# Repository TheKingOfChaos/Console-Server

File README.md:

# USB Console Server — KiCad 10 project

48 RS-232 console ports on one Raspberry Pi: three identical boards, 16 ports each.
Built from the design record of 2026-10-10. KiCad 10.0.7. **This is Rev B** (git tag `rev-A` is the first board).

| | State |
|---|---|
| Schematic | Complete, 7 sheets (FT4232H cluster reused 4×). ERC: **0 violations** at all severities. |
| Netlist | Checked pin-by-pin against the design intent (`tools/verify_netlist.py`): 255 nets, 0 mismatches. |
| PCB | **150 × 155 mm**, 4 layers, all 361 footprints placed, **fully routed**, ~3330 track segments, ~1170 vias. USB pairs coupled, length-matched and all on F.Cu (below). |
| PCB DRC | **0 errors, 0 unconnected**, 0 schematic-parity issues. Warnings: silkscreen overlaps only. |
| BOM | `bom/usb-console-server_bom.csv`. Every line has an LCSC number. |

## What changed in Rev B

- **Bring up each section on its own.** Every section gets its power through a **3-pin header: 1 = supply, 2 = section, 3 = GND**:

  | Header | Section | Supply |
  |---|---|---|
  | J11 | 5 V buck (input side) | +24V |
  | J12 | 3.3 V buck (input side) | +24V |
  | J13 | USB hub, its EEPROM and crystal (+3V3_HUB) | +3.3V |
  | J14–J17 | FT1–FT4 clusters: FT4232H, EEPROM, both MAX3232E (VCC3) | +3.3V |

  - **Jumper on 1–2** = normal running (7 jumper caps per board, LCSC C100114).
  - **Jumper off**: the section is unpowered. Put an ammeter across 1–2 to read its current, or feed it from a bench supply on 2–3.
  - A jumper put on 2–3 by mistake only grounds the dead section; it cannot short a supply.
  - The Pi needs no header: it is simply not plugged in for early bring-up.
- **Power LEDs** (green, ~1 mA) on +24V, +5V, +3.3V, +3V3_MCU (a labelled column on the left edge), PI_5V and the MCU heartbeat (right of the Pi), the hub (by J13) and each cluster (by its header).
- **Current and voltage sense:** an INA219 behind a shunt on each buck output, 5 mΩ on +5V (U23, I²C 0x40) and 10 mΩ on +3.3V (U24, 0x41). They sit on the MCU's own I²C bus (PA5/PA6, bit-banged, powered from +3V3_MCU), which replaces the old 5 V / 3.3 V ADC dividers. The buck feedback is taken before the shunt.
- **24 V screw terminal J10** (5.08 mm, 2-pin, 18 A) on the left edge, wired to +24V_RAW like the chain connectors: wire up one board, and the chain feeds the rest.
- **MCU UART header J19** (TX PB2 – GND – RX PB3). It shares the SPARE lines of the link, so debug one board at a time.
- **Test points** for each cluster's VCC3 and the INA bus (36 in total).
- **Layout:** the board grew to 150 × 155 mm. The hub moved to the top middle, so the four USB pairs drop straight down to their clusters, all on F.Cu with no vias. Each buck's power stage (inductor, catch diode, output caps, shunt, INA219) is now placed by hand: in Rev A the autoplacer had put the output caps 70 mm from the inductors.

## Sheets

| Sheet | Contents |
|---|---|
| `power` | 24 V terminal J10, input protection (F2 → Q2 → D3 → C46), board-to-board power J3/J4, 5 V and 3.3 V bucks behind bring-up headers J11/J12, shunts + INA219s, rail LEDs, LM317 MCU rail |
| `pi` | 2×20 Pi socket, LM74700 ideal diode + Q1, PI_5V bulk + TVS, HAT ID EEPROM, Pi console SP3232 + J6 |
| `hub` | USB-C, PRTR5V0U2F (inline), USB2514BI in I²C-EEPROM mode, 24 MHz crystal, 24LC02B |
| `ftdi` (×4: FT1–FT4) | FT4232HL, 12 MHz crystal, 93LC46B, two MAX3232E → 4 RS-232 ports |
| `ports` | One HC-RJ45-059D 2×8 block (16 units + shell), shield 0R / 1M / C option |
| `mcu` | ATtiny3216, ID straps, 24 V divider, JP2, INA bus pull-ups, status LED, UPDI, UART header J19, inter-board signal link J8/J9 |

Reference designators the record names are kept: F2, Q1, Q2, R9, R28, R34, R43, D3, D4, C24, C46, C62, C63, C174, X1, JP2, U10–U17.

## Decisions and departures from the record — please review

1. **RJ45 quantity.** LCSC C46261623 is a single 2×8 ganged block with all 16 jacks (~115 mm wide), not a 2-jack block. The BOM has **1 per board**, not 8.
2. **Buck converters** (the record leaves them open). **TPS54560B** (+5V, 5 A) and **TPS54360B** (+3.3V, 3.5 A): both 60 V-rated (above the 42.1 V TVS clamp), with Eco-mode pulse skipping, so they are stable unloaded on boards 2 and 3. Both run at 400 kHz, with EN left open (internal pull-up).
   **Compensation (16.9k / 4.7 nF / 47 pF) is a starting point. Re-derive it in TI WEBENCH** for the chosen L and Cout.
   Inductors are TAI-TECH TMPC1265HP-100MG-D (5 V, Isat 15.5 A; SRP1265A-100M equivalent, same 13.5 × 12.5 mm body) and SRP7028A-100M (3.3 V, Isat 6 A). Output caps are 22 µF/25 V 1206 (a JLCPCB Basic part): 4 on +5V, 3 on +3.3V.
   The LMR33630 was rejected: its 36 V rating is below the clamp.
3. **USB2514B CRFILT/PLLFILT.** The record says 0.01 µF + 0.1 µF. The datasheet asks for ≥1.0 µF low-ESR on each. **Fitted 1 µF + 100 nF. Confirm.**
4. **LM74700 VCAP** goes to ANODE (one of the record's open items; resolved per the datasheet).
5. **Pi mounting: face down on top of the board** (your choice, option B).
   - The Pi sits above our board on four M2.5 × 11 mm standoffs (H5–H8), upside down: its own GPIO header plugs down into J2, a 2×20 socket on our top side.
   - It is turned 90° so the USB/Ethernet block hangs past our top edge. The side edges stay free for the chain, so the Pi board can sit anywhere in it.
   - The Pi's underside faces up, so the **microSD card is reachable without unbolting anything**. It sits at the end toward the FTDI clusters.
   - The builder checks that J2 pad *n* sits under Pi GPIO pin *n* (the face-down Pi is a mirror image of its own top view).
   - The Pi's components face down into the 11 mm gap. **Only parts ≤ 3 mm tall sit under it**, and the builder checks this. The Pi 4 PoE-header spot (approximate, on User.Drawings) is kept clear.
   - The Pi outline and jack block are drawn on User.Drawings and F.Fab.
   - The cabinet needs ~23 mm of clearance beyond board 1's top edge for the jacks and cables.
6. **Board-to-board connectors.** With KiCad's stock right-angle header (J3/J8, right edge) and socket (J4/J9, left edge), pin *n* lands at the same height on both footprints. So the numbering runs the same direction, unlike the record's note, which describes its own footprints. The builder asserts this.
7. **RJ45 port mapping.** Column *j* (0–7, left to right) is P(2j+1) = pads 24j+1..8 and P(2j+2) = pads 24j+9..16. Pads 1/16 sit at the same end, matching the record. **Which physical jack (upper or lower) carries pads 1–8 is not in the vendor data.** The 3–6 loopback at bring-up settles it.
8. **Added parts** the record didn't specify:
   - RESET_REQ: 100k pull-down, for a defined level on boards without a Pi.
   - HAT EEPROM: ID_SD/ID_SC 3.9k pull-ups, plus a WP pull-up and write-enable jumper.
   - VBUS_DET: 47k/100k divider.
   - USB shield: 1M ‖ 4.7 nF to GND.
   - Hub RESET_N: 10k pull-up and 100 nF.
   - Hub LOCAL_PWR: 10k pull-up.
9. **Net classes:**
   - `USB_90R` (0.16 mm width / 0.15 mm gap) assumes JLCPCB's JLC04161H-3313 stackup. Confirm it in their impedance calculator.
   - `HV_24V`: 0.8 mm width, 0.3 mm clearance.
   - `Power`: 0.6 mm width.
10. **USB port swap (PRTSP) — must be set in the hub EEPROM.** On the hub and on the FT4232Hs, D− sits above D+ on the faces that point at each other, so a coupled pair would have to cross over. Instead, D+/D− are swapped at the hub's downstream pins in the schematic (pin 1 = D+ of port 1, pin 2 = D−, and so on for pins 1–4 and 6–9).
    - The USB2514B undoes the swap internally when **PRTSP (register 0xFA) = 0x1E** (ports 1–4) in the 24LC02B image.
    - **Without it, none of the FT4232Hs will enumerate.**
    - The upstream port is not swapped (bit 0 stays 0).

## Board layout

150 × 155 mm: the 115 mm RJ45 block along the bottom, a slotted M3 chassis hole in each corner.

- **Bottom edge.** The RJ45 block, front flush with the edge. Silkscreen `P02 / P01`, etc. above each column.
- **Middle band.** FT1–FT4 clusters, each over its own two jack columns (FT1 at the P01 end): MAX3232E row next to the jacks, then the FT4232H with its crystal and decoupling, then the EEPROM. Above each cluster: its bring-up header (`FT1 3V3` ...) and power LED.
- **Edge strips beside the clusters.** Board-to-board connectors: J8 (link) and J3 (24 V) headers on the right, J9/J4 sockets on the left, same heights. J10, the 24 V screw terminal, sits above J9 with its wire openings at the left edge.
- **Top left: power.** J11/J12 bring-up headers and the rail LEDs on the left edge; the 5 V buck (U8, L1, D1, output caps, shunt R10, INA219 U23) and below it the 3.3 V buck (U9, L2, D2, caps, R11, U24); the 24 V protection (F2, Q2, C46) next to the terminal.
- **Top middle: USB.** USB-C J1 on the top edge near the Pi's USB-A ports, the PRTR5V0U2F, the hub U5 with its crystal and EEPROM, J13 (hub bring-up header). A clear corridor below the hub carries the four USB pairs to the clusters.
- **Top right.** The Raspberry Pi, face down above the board (X 84–140, Y 0–65), with its jacks over the top edge; J2 runs down its right side. Under the Pi: the MCU, Pi console transceiver, HAT EEPROM, ideal diode and LM317 (all low parts). In the 10 mm strip right of it: UPDI J7, Pi console J6, MCU UART J19, the PI_5V electrolytics and the MCU / PI5V LEDs.

## Test points

36 bare pads (no BOM cost), all reachable with the Pi fitted. The board builder keeps them out from under the Pi.

| Where | Test points |
|---|---|
| Rails | +24V_RAW, +24V, +5V, +3.3V, +3V3_MCU, PI_5V, PI3.3, and per cluster its VCC3 and 1.8 V VCORE (×4) |
| Ground | by the bucks, by the USB-C input, beside the jacks (scope ground), and one per cluster |
| Buses | PI_SDA / PI_SCL, HUB_SDA / HUB_SCL, INA_SDA / INA_SCL |
| Control | HUB_MR_N, FTDI_RST_N, RESET_REQ, ALERT, VBUS_UP, MCU spare PA7 |
| Pi console | PITXD / PIRXD (TTL side; the RS-232 side is on J6) |

## Stackup and routing

**Stackup** (JLCPCB 4-layer):
- F.Cu: signals, plus ground pour.
- In1.Cu: solid ground plane.
- In2.Cu: signals, plus a +3.3V pour and a +5V band.
- B.Cu: signals, plus ground pour.

**Rules:** JLCPCB standard 4-layer: 0.127 mm track and space, 0.5/0.25 mm signal vias.

**Routing pipeline:** `tools/route.py`, then `tools/close_gaps.py`.

1. **Pre-routing** (locked):
   - every FT4232H ground pin gets an inward stub and a via to the ground plane;
   - the four hub→FT4232H USB pairs are routed first as coupled pairs (`tools/diffpair.py`, 0.16 mm / 0.15 mm gap), see "USB pairs" below.

   This stops anything else boxing those 0.5 mm-pitch pins in.
2. **Freerouting 2.4** routes everything else, with these net-class widths:

   | Net class | Width | Nets |
   |---|---|---|
   | USB_90R | 0.16 mm | USB pairs |
   | Power | 0.3 mm | power nets |
   | HV_24V | 0.5 mm | 24 V |
   | Chain24V | 1.0 mm | the 24 V pass-through between J3 and J4 |
   | HighCurrent | 0.6 mm | 5 V path and switch nodes |

3. **Power copper** carries the real current; the traces only guarantee connectivity:
   - pours on both buck switch nodes, both buck inputs, both buck outputs (up to the shunts) and the ideal-diode input;
   - a 7 mm-wide +5V band on In2 from the 5 V shunt to the Pi, stitched with vias at both ends;
   - an In2 pour per switched section (+3V3_HUB, each cluster's VCC3) over that section.
4. **Ground stitching:** a 4 mm via grid across the board, and a via grid under each FT4232H and the hub.
5. **Cleanup** (`close_gaps.py`), driven by KiCad's own DRC report:
   - joins the autorouter's near misses;
   - gives stranded ground or +3.3V pads a via to their plane or pour;
   - maze-routes anything still open, ripping up the nets that wall it in if needed;
   - removes any via that violates clearance.

**USB pairs (hub → FT4232H), routed as coupled pairs, all on F.Cu over the In1 ground plane, no vias:**

| Port | D+ | D− | Skew |
|---|---|---|---|
| 1 | 97.4 mm | 96.2 mm | 1.1 mm |
| 2 | 82.4 mm | 81.2 mm | 1.1 mm |
| 3 | 83.2 mm | 82.1 mm | 1.1 mm |
| 4 | 89.4 mm | 87.5 mm | 1.9 mm |
| upstream (USB-C → hub) | 17.1 mm | 18.0 mm | 0.9 mm |

- 1–2 mm of skew is ≈ 7–13 ps; USB 2.0 high speed tolerates far more, so no tuning meanders were added.
- The pair router keeps the pairs clear of the bucks' whole power stage and never routes under an IC body.
- This depends on the **PRTSP = 0x1E** hub setting (decision 10).
- Hand fixes after the generated routing (so `build_all.sh` alone does not reproduce this board exactly): FT1's VPHY escapes through a 0.45 mm via at pin 4 (its VCORE B.Cu track was moved 0.55 mm to make room), TP12 moved 0.6 mm, one GND stitching via in an isolated F.Cu pour island.

**Review before ordering:**
- **USB pair impedance:** 0.16 mm / 0.15 mm gap is ≈ 90 Ω differential on JLC04161H-3313 (F.Cu over In1). Confirm it in JLCPCB's impedance calculator.
- **Buck loops:** the power stages are now placed by hand, but still check each input-cap / switch / diode loop against the TPS54x60 layout guide.
- **INA219 shunt routing:** IN+/IN- are routed from the shunt pads by the autorouter; check they are Kelvin connections (from the shunt pads themselves, not from the pour).
- **Autorouted traces:** the routing is generated, so expect some odd detours. Re-run DRC after any hand edit.

## 3D model

- `3d/usb-console-server.step`: the whole board with every part (16 MB), for enclosure design in any CAD tool. `3d/preview.png` is a quick render.
- Rebuild it in KiCad (File > Export > STEP) or with `kicad-cli pcb export step --subst-models usb-console-server.kicad_pcb`; KiCad's standard 3D library must be installed.
- Models that are not in KiCad's library are in `lib/console_server.3dshapes`:
  - **J5, the 16-port RJ45 block, is a simplified envelope** (`tools/rj45_model.py`): no vendor model or drawing exists. The 115 × 28.2 mm outline and port positions match the footprint, but the **25.4 mm height is assumed** (typical for stacked 2×N RJ45). Measure a real part before finalising an enclosure.
  - L2 (SRP7028A) and J1 (HRO TYPE-C-31-M-12 USB-C) use the EasyEDA models for their LCSC parts.
  - `tools/fix_3d_models.py` points L2, J1, U8 and U9 at these files (KiCad 10 renamed or lacks the stock ones).
- The Raspberry Pi is not in the model. It sits face-down on J2.

## Ordering from JLCPCB

`python3 tools/jlc_export.py` writes `jlcpcb/`:

| File | Upload as |
|---|---|
| `usb-console-server_gerbers.zip` | the PCB: 4 layers, 150 × 155 mm, 1.6 mm, impedance control with stackup **JLC04161H-3313** |
| `usb-console-server_bom_jlc.csv` | assembly BOM: 65 lines, every one with an LCSC number (SMD only) |
| `usb-console-server_cpl_jlc.csv` | pick-and-place: 293 parts, all on the top side |
| `usb-console-server_hand_solder.csv` | not uploaded: the through-hole connectors you solder yourself, with LCSC numbers to buy them |
| `usb-console-server_lcsc_order_3boards.csv` | LCSC BOM Tool upload: **every** part for a full set of 3 boards (to build them all yourself) |
| `usb-console-server_lcsc_order_3boards_through_hole_only.csv` | LCSC BOM Tool upload: only the hand-soldered connectors and jumper caps, when JLCPCB assembles the SMD parts |
| `..._5boards.csv`, `..._5boards_through_hole_only.csv` | the same for 5 boards |

- Other board counts: `python3 tools/lcsc_order.py <boards>`. LCSC rounds each line up to its minimum order quantity.
- **Not assembled by JLC:** test points, mounting holes and DNP parts, and every through-hole part (J2 Pi socket, J3/J4 power chain, J5 RJ45 block, J8/J9 link, J6/J7/J19 debug headers, J10 terminal, J11–J17 bring-up headers) plus the 7 jumper caps. These are soldered by hand; see `usb-console-server_hand_solder.csv`.
- **Check every part's rotation in JLC's placement preview.** KiCad and JLC disagree on the zero orientation of some packages (often SOT-223, SOT-23-6, SOIC, the LQFP/QFN ICs, diodes, electrolytics, crystals). Fix any that look wrong in their editor before paying.
- Stock and "extended part" fees change daily; JLC flags missing parts when you upload the BOM.

## Regenerating

Everything is generated from `tools/design.py` (schematic) and `tools/build_pcb.py` (board), which need KiCad 10 with its Python module. `tools/build_all.sh` rebuilds and re-verifies the whole project.

**Rebuilding overwrites the board placement.** Once you start editing the PCB by hand, treat the KiCad files as the source and stop regenerating.

## Bring-up checklist

Start with **every bring-up jumper off** (J11–J17) and no Pi.

1. **24 V input.** 24 V on J10 with a current-limited supply: the 24V and MCU LEDs light, nothing else. Then reverse polarity: nothing downstream may see voltage.
2. **MCU alone** (it runs from its own LM317): UPDI on J7, heartbeat LED, ID straps read with a meter, J19 UART.
3. **5 V buck:** jumper J11. 5V LED on, 5.09 V at TP +5V, stable with no load (it is unloaded on boards 2 and 3 for life). INA219 U23 at 0x40 on the MCU's INA bus.
4. **3.3 V buck:** jumper J12. 3V3 LED on, 3.33 V, INA219 U24 at 0x41.
5. **Hub:** jumper J13 (meter across 1–2 first: expect ~50–100 mA). Program the hub EEPROM (**including PRTSP = 0x1E**), then `lsusb` from a PC shows the hub.
6. **One cluster at a time:** jumper J14 (FT1), check its current on 1–2 (~70–150 mA), `lsusb` shows the FT4232H, program its EEPROM serial (`HUB<b>-P<n>`), then J15–J17.
7. **Pi:** fit it on one board, PI5V LED, `i2cdetect -y 1` shows 0x30.
8. **Loopback** (pin 3 ↔ pin 6) on every port, including one upper and one lower jack early.
9. udev rules.
10. Chain boards 2 and 3.

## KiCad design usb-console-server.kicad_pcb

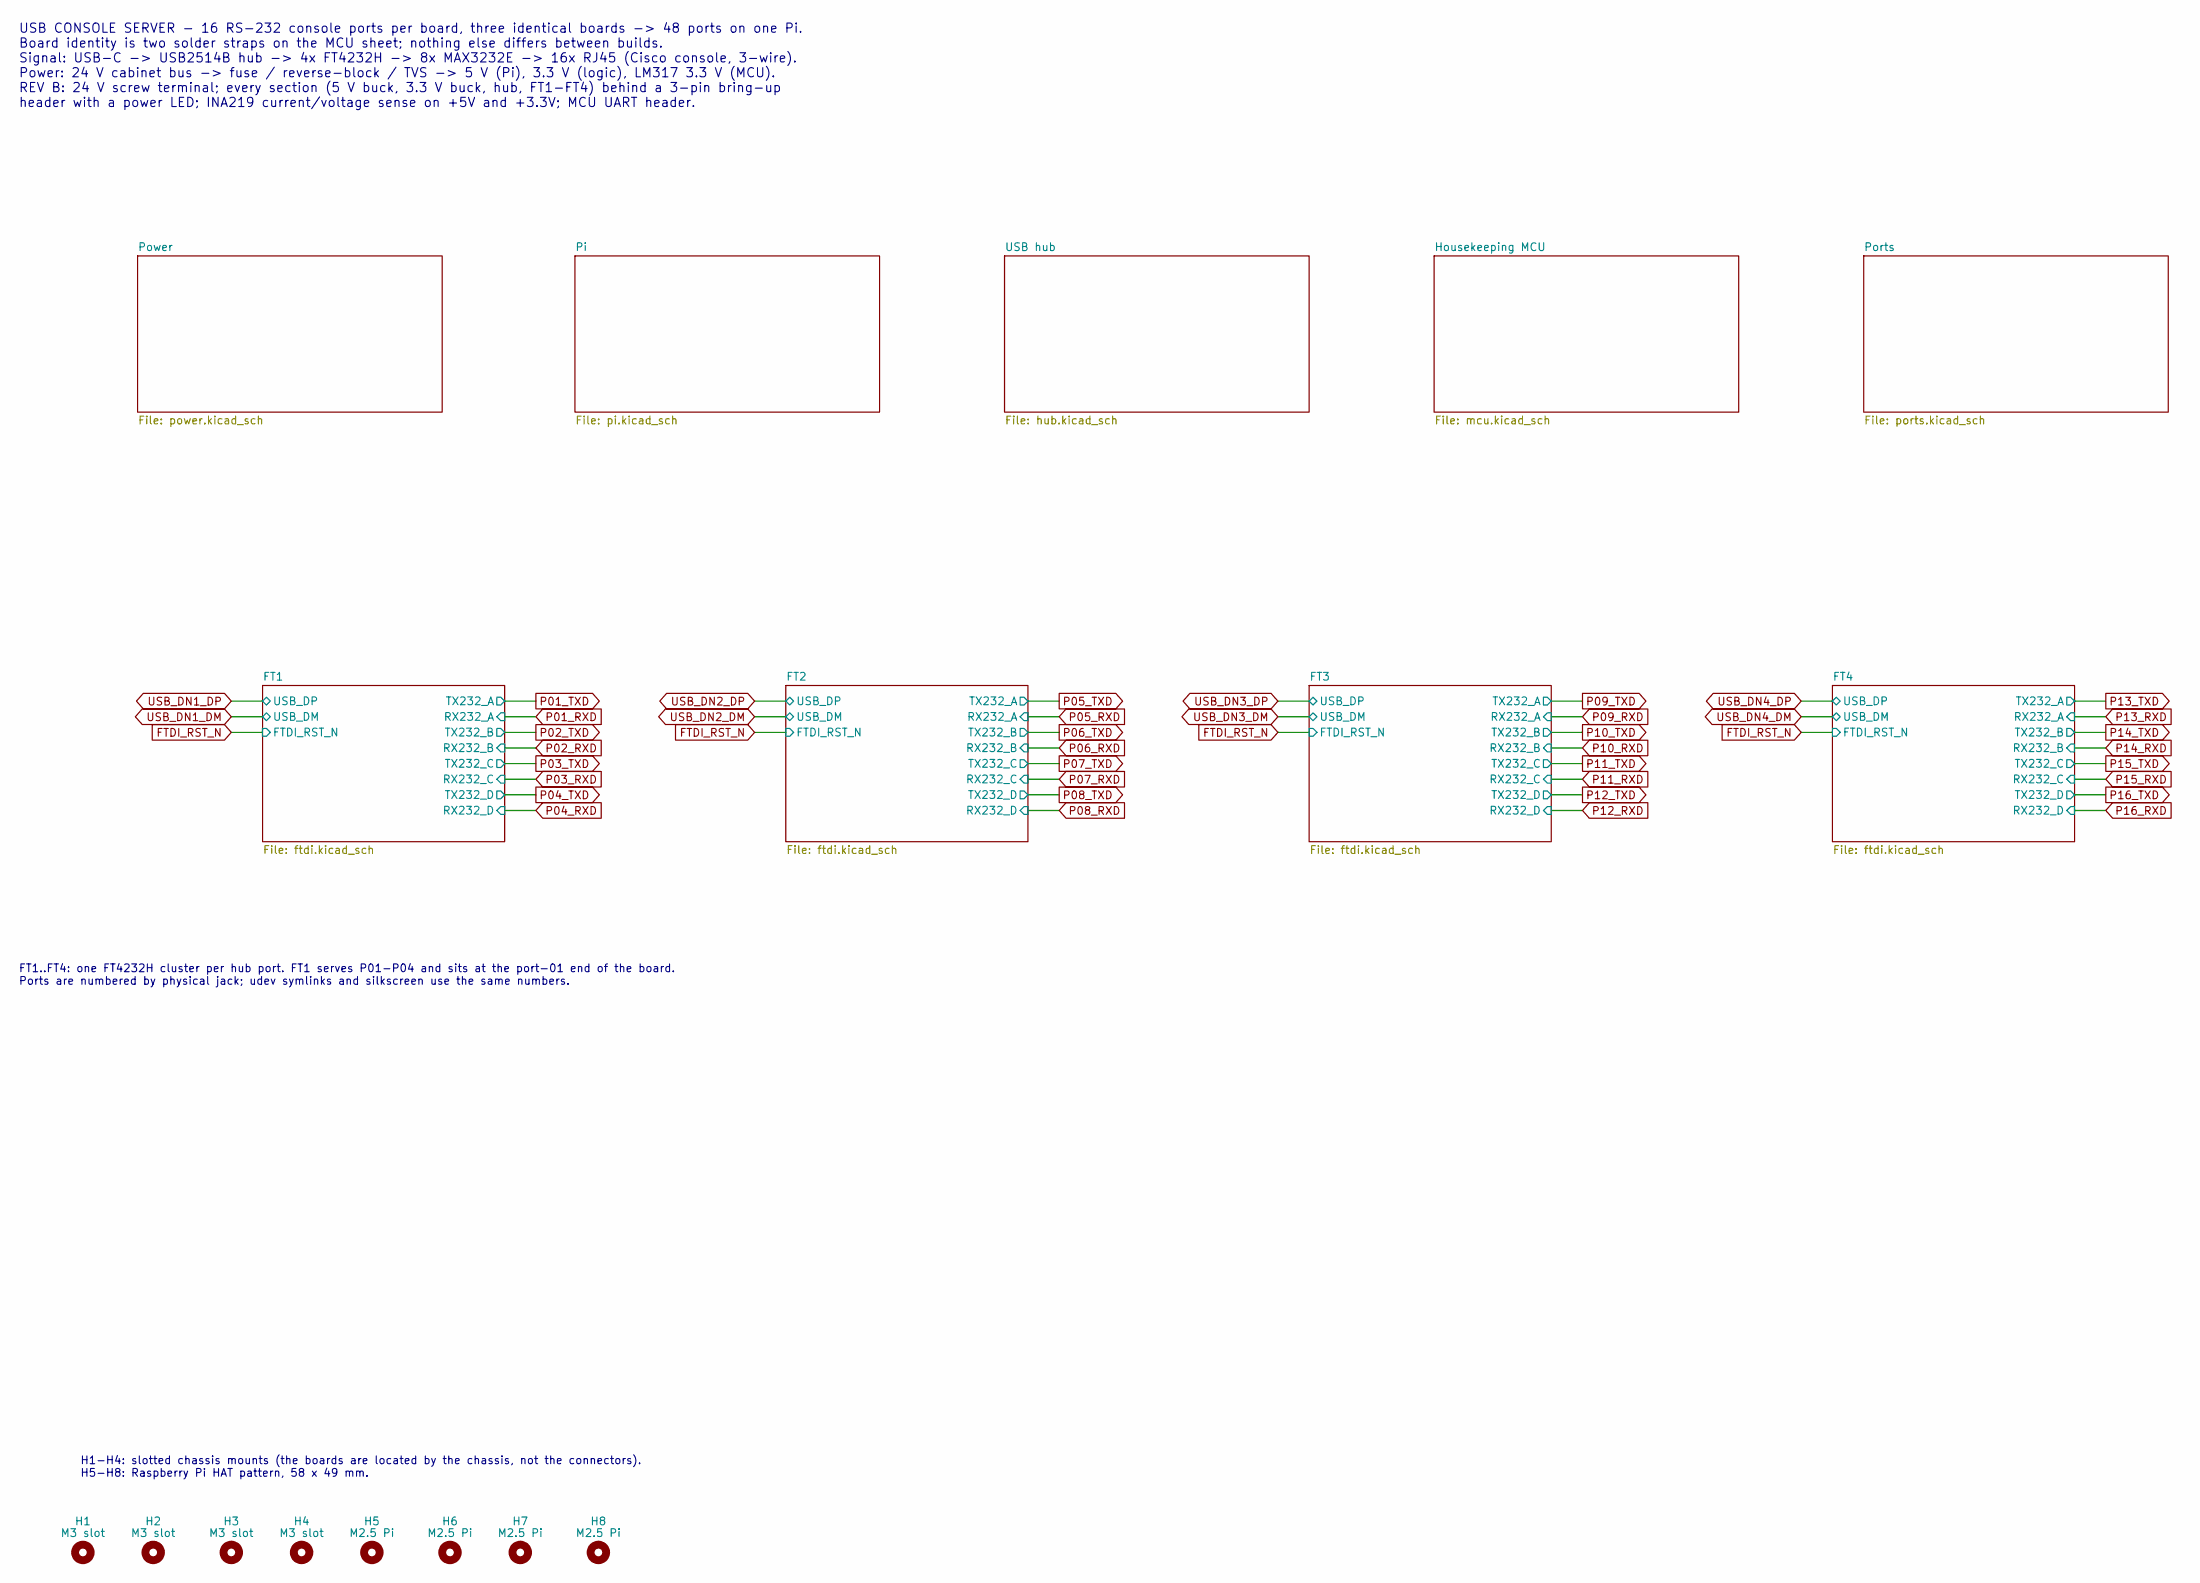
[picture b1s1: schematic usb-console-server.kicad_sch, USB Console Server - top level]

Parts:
H1, H2, H3, H4: M3 slot; MountingSlot_3.2x6mm
H5, H6, H7, H8: M2.5 Pi; MountingHole_2.7mm_M2.5

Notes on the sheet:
USB CONSOLE SERVER - 16 RS-232 console ports per board, three identical boards -> 48 ports on one Pi. Board identity is two solder straps on the MCU sheet; nothing else differs between builds. Signal: USB-C -> USB2514B hub -> 4x FT4232H -> 8x MAX3232E -> 16x RJ45 (Cisco console, 3-wire). Power: 24 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
FT1..FT4: one FT4232H cluster per hub port. FT1 serves P01-P04 and sits at the port-01 end of the board. Ports are numbered by physical jack; udev symlinks and silkscreen use the same numbers.
H1-H4: slotted chassis mounts (the boards are located by the chassis, not the connectors). H5-H8: Raspberry Pi HAT pattern, 58 x 49 mm.

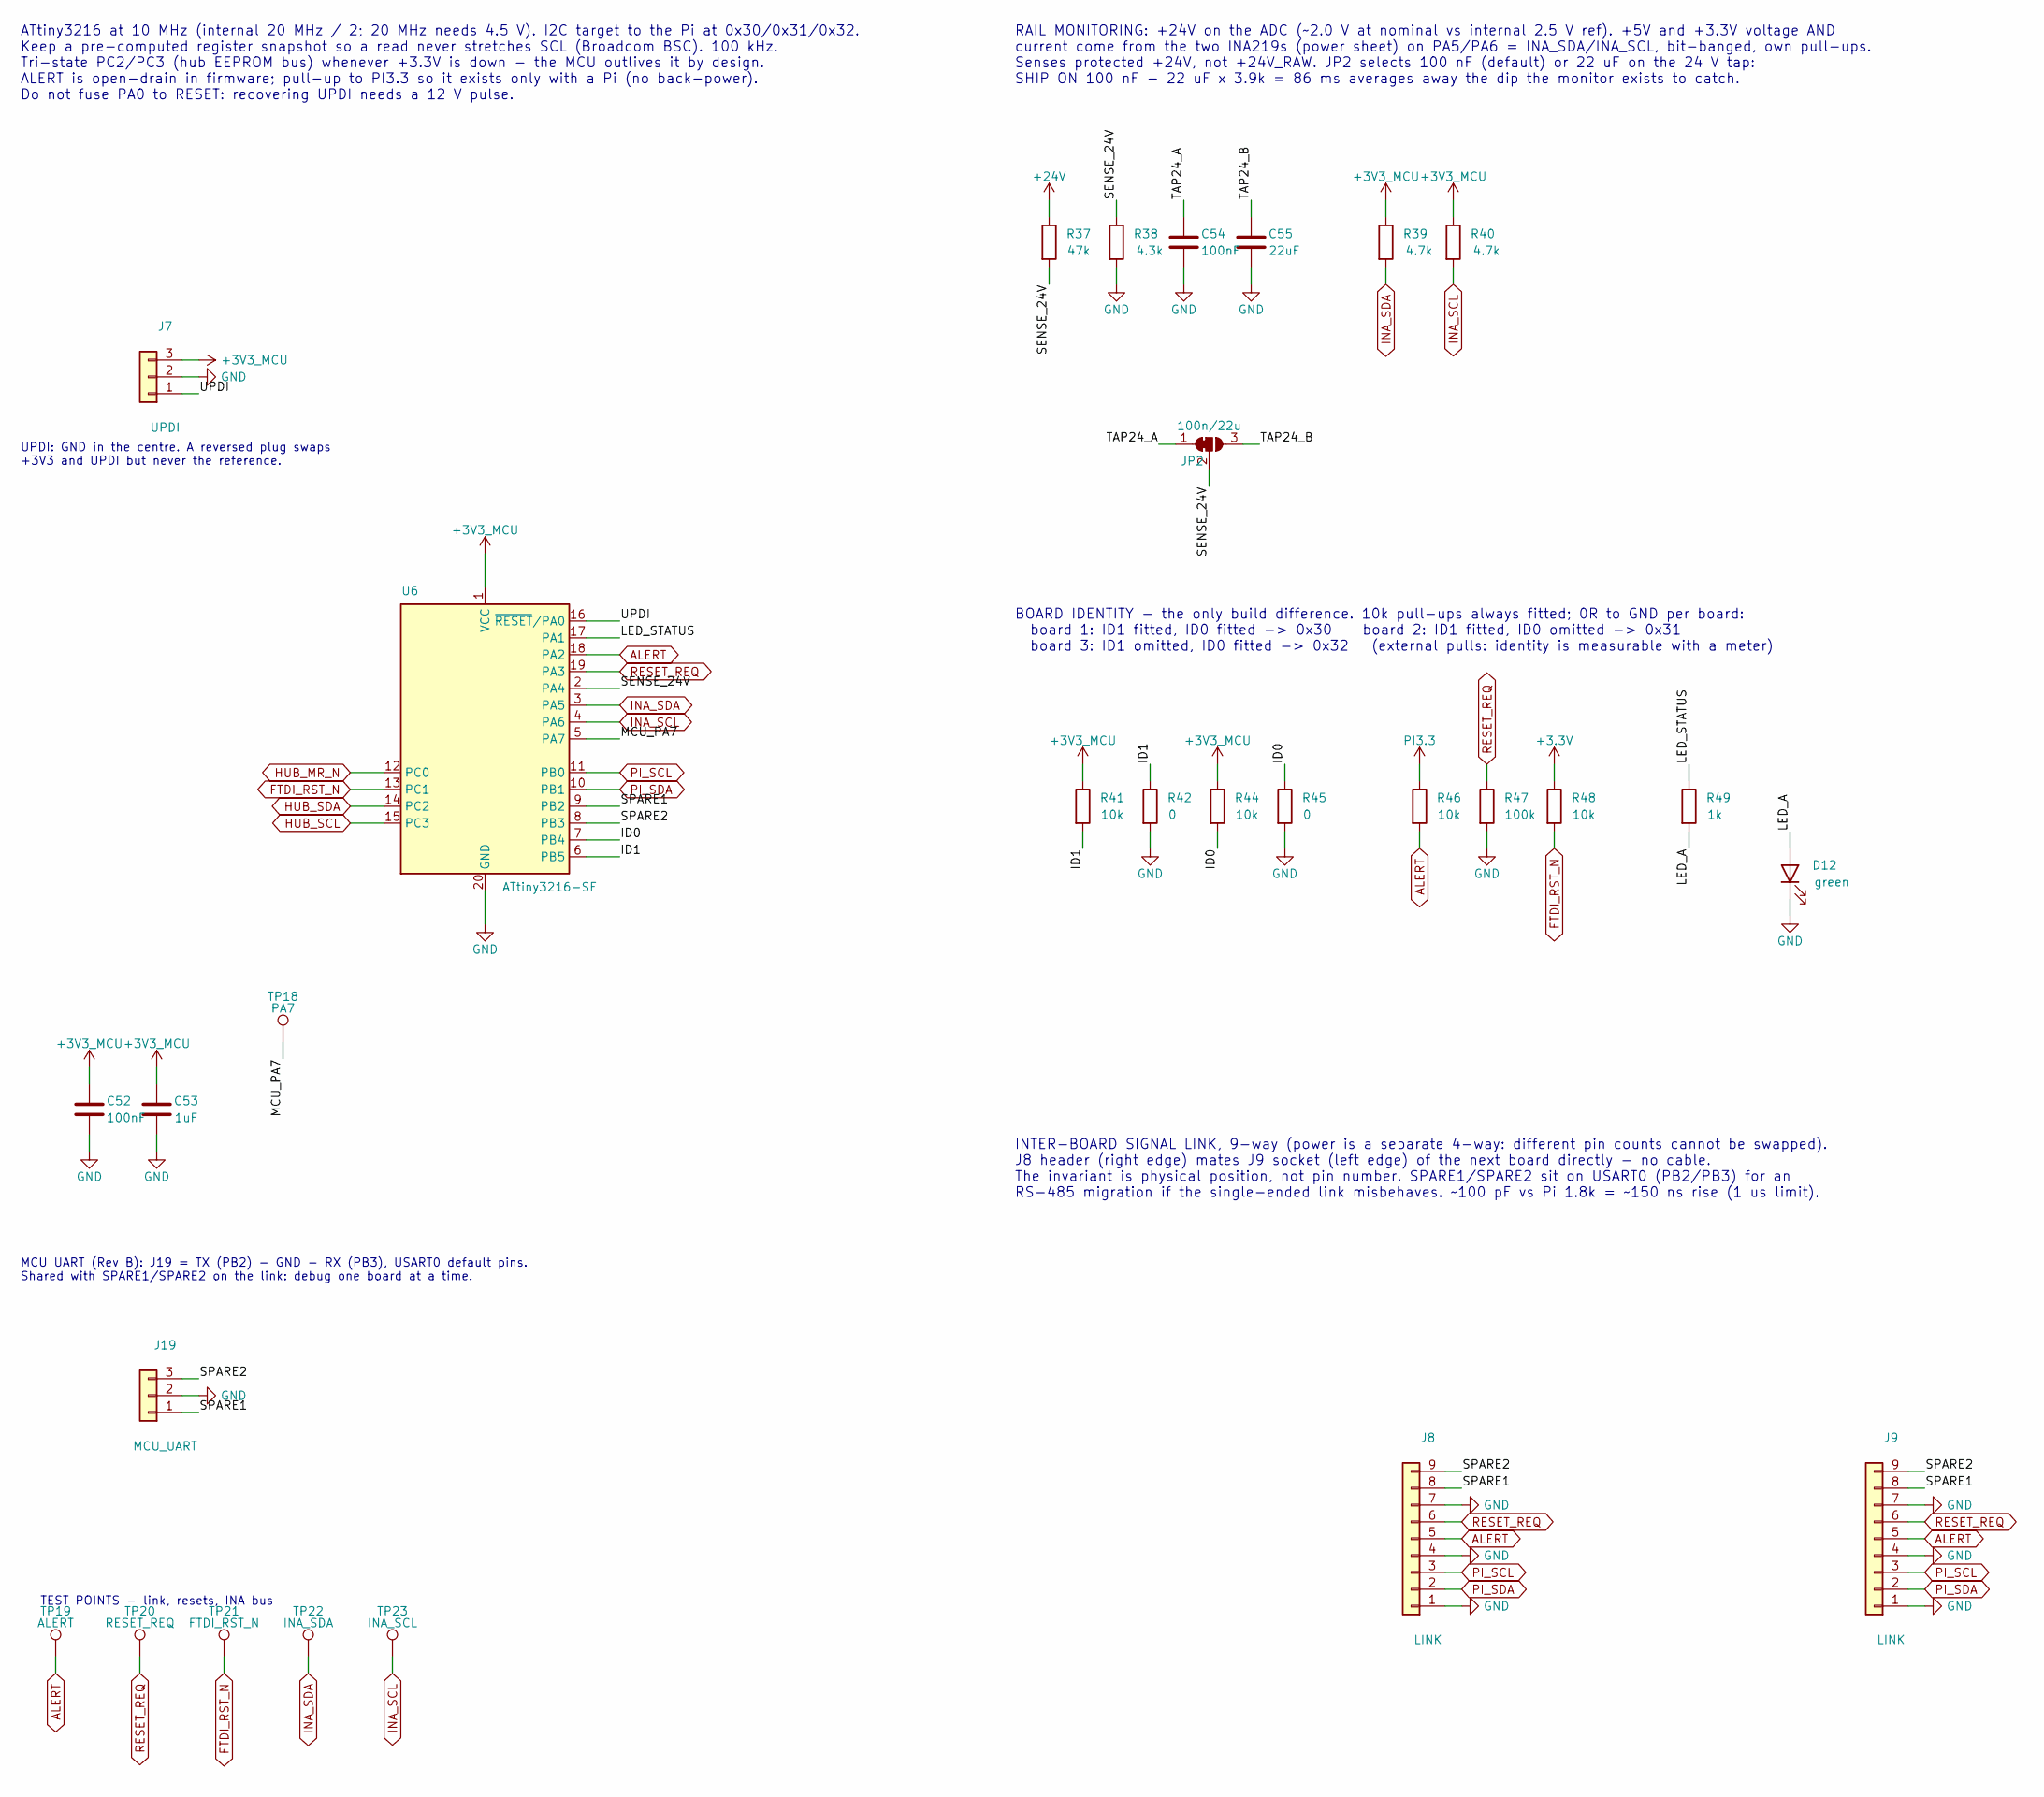
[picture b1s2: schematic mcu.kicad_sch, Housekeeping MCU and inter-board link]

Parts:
C52, C54: 100nF; C_0603_1608Metric; LCSC C14663
C53: 1uF; C_0603_1608Metric; LCSC C29936
C55: 22uF; C_1206_3216Metric; LCSC C77091
D12: green; LED_0603_1608Metric; LCSC C965805
J7: UPDI; PinHeader_1x03_P2.54mm_Vertical; LCSC C49257
J8: LINK; PinHeader_1x09_P2.54mm_Horizontal; LCSC C492417
J9: LINK; PinSocket_1x09_P2.54mm_Horizontal; LCSC C2897391
J19: MCU_UART; PinHeader_1x03_P2.54mm_Vertical; LCSC C49257
JP2: 100n/22u; SolderJumper-3_P1.3mm_Bridged12_RoundedPad1.0x1.5mm
R37: 47k; R_0603_1608Metric; LCSC C111134
R38: 4.3k; R_0603_1608Metric; LCSC C23159
R39, R40: 4.7k; R_0603_1608Metric; LCSC C23162
R41, R44, R46, R48: 10k; R_0603_1608Metric; LCSC C25804
R42, R45: 0; R_0603_1608Metric; LCSC C21189
R47: 100k; R_0603_1608Metric; LCSC C25803
R49: 1k; R_0603_1608Metric; LCSC C22548
TP18: PA7; TestPoint_Pad_D1.5mm
TP19: ALERT; TestPoint_Pad_D1.0mm
TP20: RESET_REQ; TestPoint_Pad_D1.0mm
TP21: FTDI_RST_N; TestPoint_Pad_D1.0mm
TP22: INA_SDA; TestPoint_Pad_D1.0mm
TP23: INA_SCL; TestPoint_Pad_D1.0mm
U6: ATtiny3216-SF; SOIC-20W_7.5x12.8mm_P1.27mm; LCSC C1340355

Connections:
+3.3V: R48.1; also elsewhere on the board
+3V3_MCU: C52.1, C53.1, J7.3, R39.1, R40.1, R41.1, R44.1, U6.1 (VCC); also elsewhere on the board
+24V: R37.1; also elsewhere on the board
/Housekeeping MCU/ID0: R44.2, R45.1, U6.7 (PB4)
/Housekeeping MCU/ID1: R41.2, R42.1, U6.6 (PB5)
/Housekeeping MCU/LED_A: D12.2 (A), R49.2
/Housekeeping MCU/LED_STATUS: R49.1, U6.17 (PA1)
/Housekeeping MCU/MCU_PA7: TP18.1, U6.5 (PA7)
/Housekeeping MCU/SENSE_24V: JP2.2 (C), R37.2, R38.1, U6.2 (PA4)
/Housekeeping MCU/SPARE1: J8.8, J9.8, J19.1, U6.9 (PB2)
/Housekeeping MCU/SPARE2: J8.9, J9.9, J19.3, U6.8 (PB3)
/Housekeeping MCU/TAP24_A: C54.1, JP2.1 (A)
/Housekeeping MCU/TAP24_B: C55.1, JP2.3 (B)
/Housekeeping MCU/UPDI: J7.1, U6.16 (~RESET/PA0)
ALERT: J8.5, J9.5, R46.2, TP19.1, U6.18 (PA2); also elsewhere on the board
FTDI_RST_N: R48.2, TP21.1, U6.13 (PC1); also elsewhere on the board
GND: C52.2, C53.2, C54.2, C55.2, D12.1 (K), J7.2, J8.1, J8.4, J8.7, J9.1, J9.4, J9.7, J19.2, R38.2, R42.2, R45.2, R47.2, U6.20 (GND); also elsewhere on the board
HUB_MR_N: U6.12 (PC0); also elsewhere on the board
HUB_SCL: U6.15 (PC3); also elsewhere on the board
HUB_SDA: U6.14 (PC2); also elsewhere on the board
INA_SCL: R40.2, TP23.1, U6.4 (PA6); also elsewhere on the board
INA_SDA: R39.2, TP22.1, U6.3 (PA5); also elsewhere on the board
PI3.3: R46.1; also elsewhere on the board
PI_SCL: J8.3, J9.3, U6.11 (PB0); also elsewhere on the board
PI_SDA: J8.2, J9.2, U6.10 (PB1); also elsewhere on the board
RESET_REQ: J8.6, J9.6, R47.1, TP20.1, U6.19 (PA3); also elsewhere on the board

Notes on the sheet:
ATtiny3216 at 10 MHz (internal 20 MHz / 2; 20 MHz needs 4.5 V). I2C target to the Pi at 0x30/0x31/0x32. Keep a pre-computed register snapshot so a read never stretches SCL (Broadcom BSC). 100 kHz. Tri-state PC2/PC3 (hub EEPROM bus) whenever +3.3V is down - the MCU outlives it by design. ALERT is op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
INTER-BOARD SIGNAL LINK, 9-way (power is a separate 4-way: different pin counts cannot be swapped). J8 header (right edge) mates J9 socket (left edge) of the next board directly - no cable. The invariant is physical position, not pin number. SPARE1/SPARE2 sit on USART0 (PB2/PB3) for an RS-485 migra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
MCU UART (Rev B): J19 = TX (PB2) - GND - RX (PB3), USART0 default pins. Shared with SPARE1/SPARE2 on the link: debug one board at a time.
BOARD IDENTITY - the only build difference. 10k pull-ups always fitted; 0R to GND per board: board 1: ID1 fitted, ID0 fitted -> 0x30 board 2: ID1 fitted, ID0 omitted -> 0x31 board 3: ID1 omitted, ID0 fitted -> 0x32 (external pulls: identity is measurable with a meter)
TEST POINTS - link, resets, INA bus
UPDI: GND in the centre. A reversed plug swaps +3V3 and UPDI but never the reference.
RAIL MONITORING: +24V on the ADC (~2.0 V at nominal vs internal 2.5 V ref). +5V and +3.3V voltage AND current come from the two INA219s (power sheet) on PA5/PA6 = INA_SDA/INA_SCL, bit-banged, own pull-ups. Senses protected +24V, not +24V_RAW. JP2 selects 100 nF (default) or 22 uF on the 24 V tap: S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
